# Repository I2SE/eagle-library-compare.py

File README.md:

eagle-library-compare.py
========================

Eagle CAD files store all libraries inside the XML files for boards and layouts (.brd and .sch). This tool is to be used to compare these embedded libraries to the external library files (.lbr).

This test is intended to be used in automatic quality assurance systems. You might find it usefull to have a hook of your version control system calling this script on each commit.

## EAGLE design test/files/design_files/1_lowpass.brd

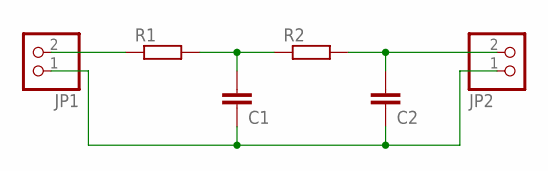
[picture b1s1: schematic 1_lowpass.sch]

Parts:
C1, C2: C-EUC1206; C1206
JP1, JP2: PINHD-1X2; 1X02
R1, R2: R-EU_M1206; M1206

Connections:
unnamed: JP1.2, R1.1
unnamed: C1.1, C2.1, JP1.1, JP2.1
unnamed: C2.2, JP2.2, R2.2
unnamed: C1.2, R1.2, R2.1

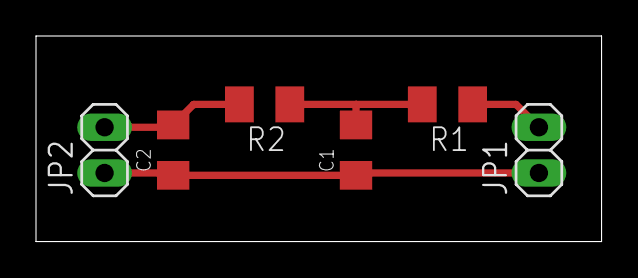
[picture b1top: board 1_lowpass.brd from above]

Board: 2 copper layers, 31.4 x 11.4 mm, 6 parts (0 on the bottom side), 4 nets.

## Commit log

2014-02-20 added meaningfull description to README file
2014-02-20 split main compare function (check_library_identity_brd) for brd files into several general functions...
2014-02-20 updated the third design file schematic to have differences in all three types of library elements (deviceset, symbol, package)
2014-02-20 added support for library elements that are in the schematic but not in the brd files...
2014-02-20 added short list of open tasks
2014-03-03 refactoring for passing pylint test
2014-03-03 updating test output compare files to make nosetest pass
2014-03-03 removing python 2.6 from list of tested python versions
2014-03-03 adding build status to readme
2014-03-03 after updating the .out files in the test cases: removing this from TODO
